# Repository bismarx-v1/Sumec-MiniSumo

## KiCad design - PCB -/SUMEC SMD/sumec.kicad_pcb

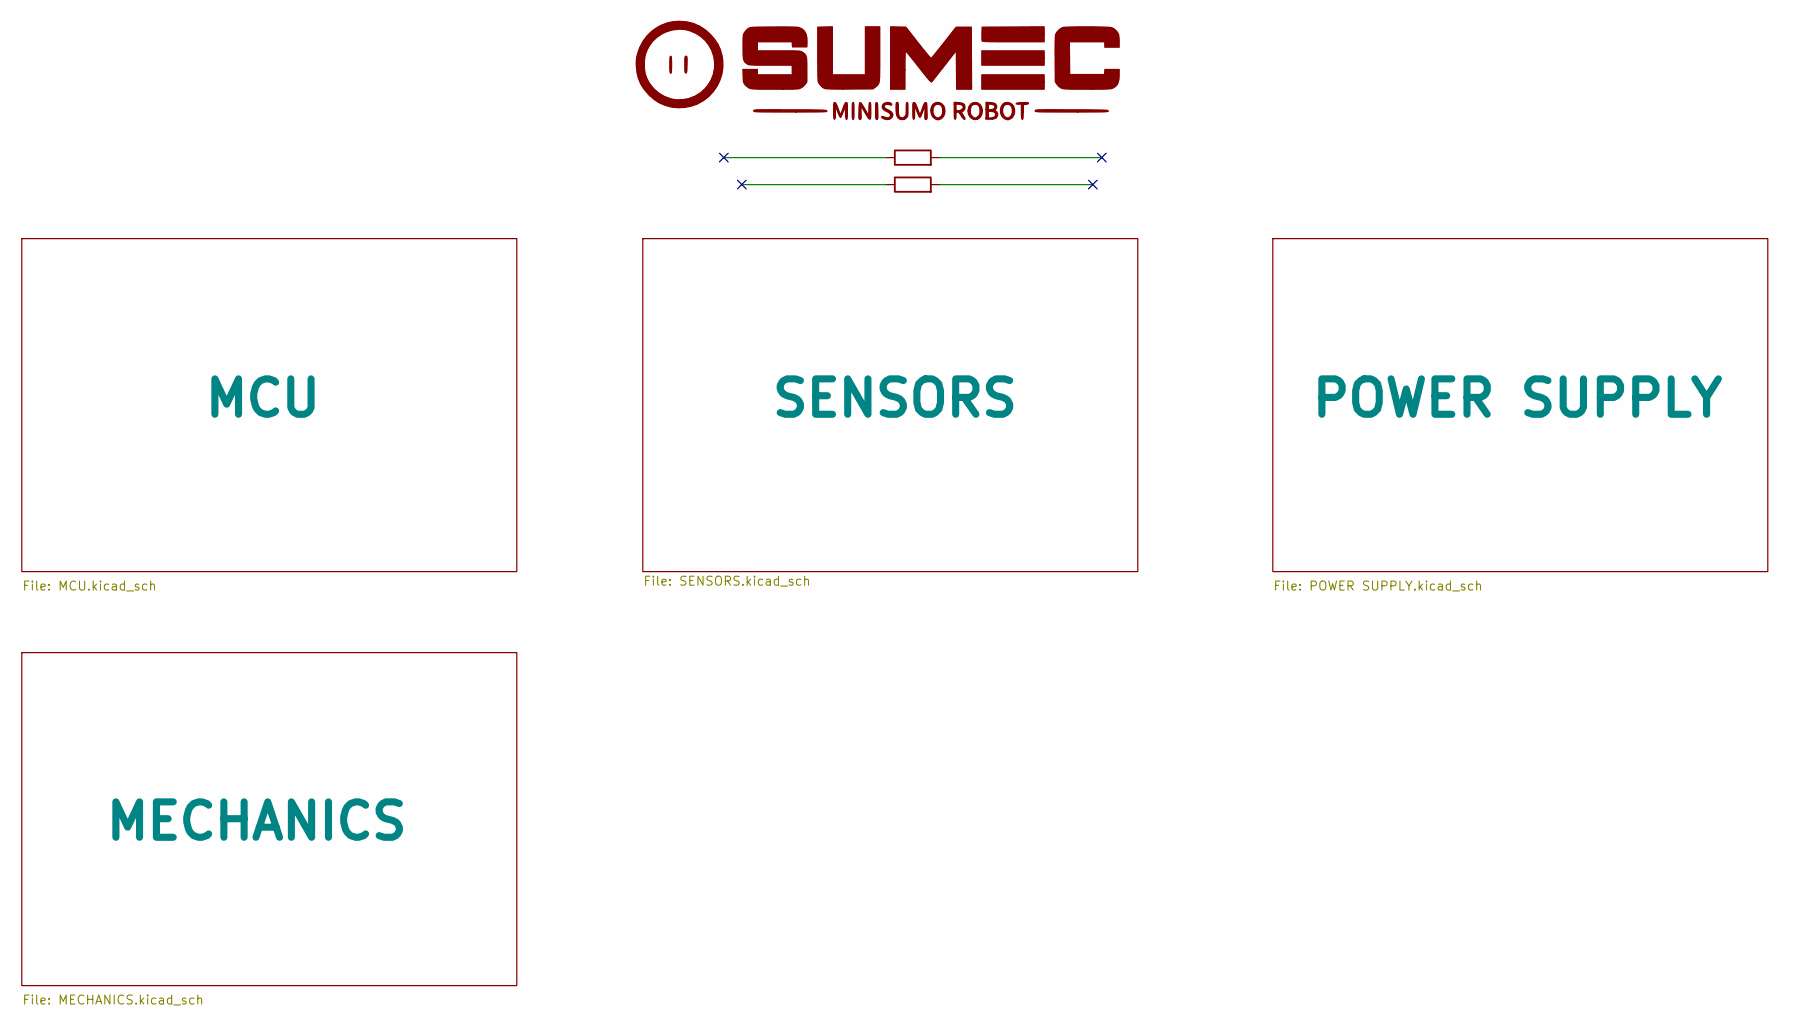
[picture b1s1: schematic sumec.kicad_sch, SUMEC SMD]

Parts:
R1: R; logo even smaller
R7: R; car cool smol

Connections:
+3V3: R7.2; also elsewhere on the board
EN: R7.1; also elsewhere on the board

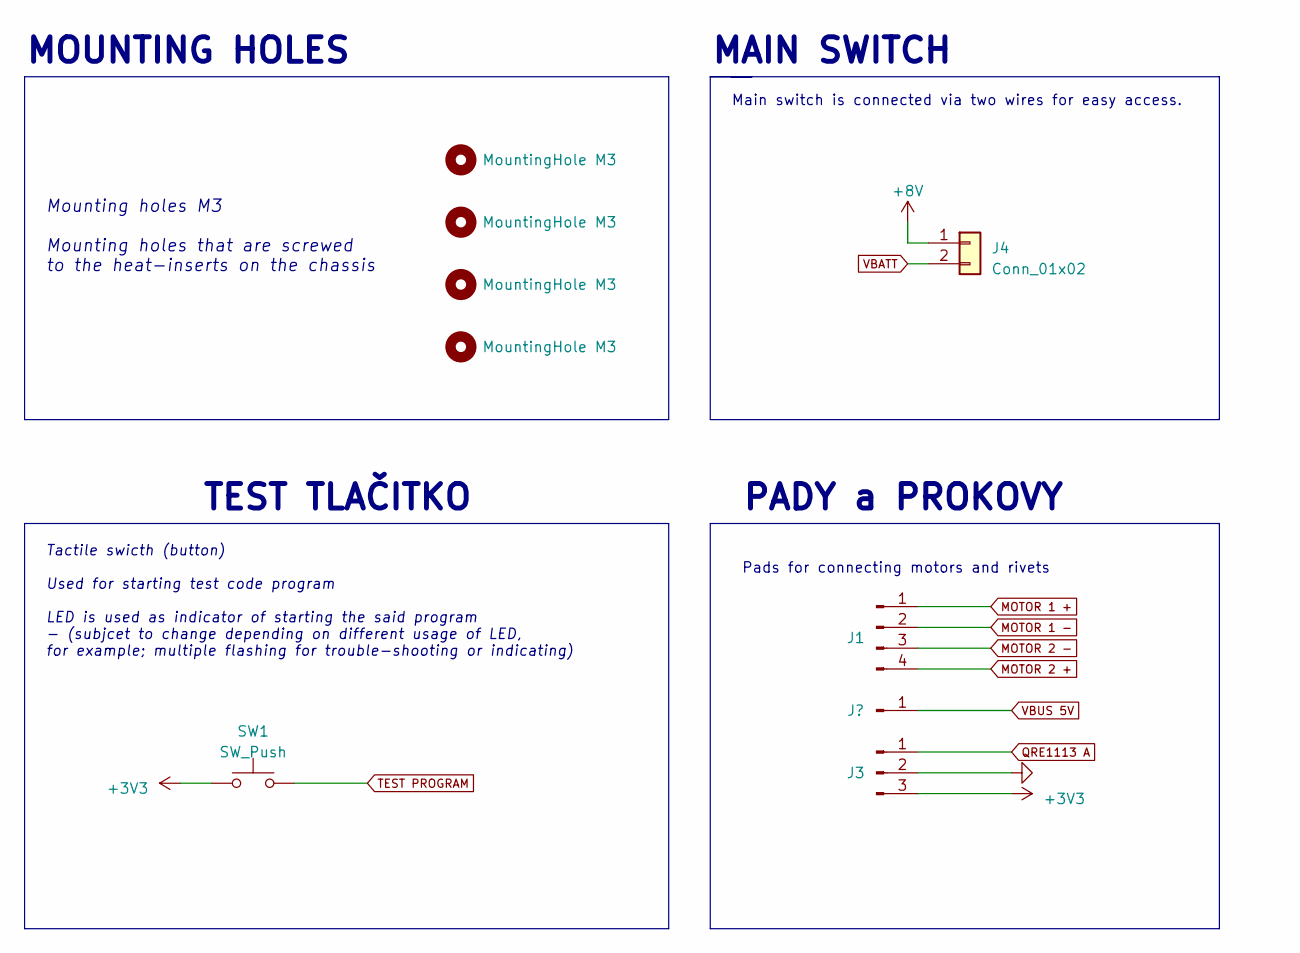
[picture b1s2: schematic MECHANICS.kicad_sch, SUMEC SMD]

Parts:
H1, H2, H3, H4: MountingHole M3; MountingHole_3.2mm_M3_ISO7380_Pad
J1: Conn_01x04_Pin; PinHeader_1x04_P2.54mm_Vertical
J2: Conn_01x01_Pin; SolderWire-0.1sqmm_1x01_D0.4mm_OD1mm
J3: Conn_01x03_Pin; PinSocket_1x03_P2.54mm_Vertical
J4: Conn_01x02; PinHeader_1x02_P2.54mm_Vertical
SW1: SW_Push; SW_SPST_B3U-1000P

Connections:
+3V3: J3.3, SW1.1; also elsewhere on the board
+8V: J4.1; also elsewhere on the board
GND: J3.2; also elsewhere on the board
MOTOR 1 +: J1.1; also elsewhere on the board
MOTOR 1 -: J1.2; also elsewhere on the board
MOTOR 2 +: J1.4; also elsewhere on the board
MOTOR 2 -: J1.3; also elsewhere on the board
QRE1113 A: J3.1; also elsewhere on the board
TEST PROGRAM: SW1.2; also elsewhere on the board
VBATT: J4.2; also elsewhere on the board
VBUS 5V: J2.1; also elsewhere on the board

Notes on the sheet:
MOUNTING HOLES
Pads for connecting motors and rivets
Mounting holes M3 Mounting holes that are screwed to the heat-inserts on the chassis
MAIN SWITCH
TEST TLAČITKO
Main switch is connected via two wires for easy access.
PADY a PROKOVY
Tactile swicth (button) Used for starting test code program LED is used as indicator of starting the said program - (subjcet to change depending on different usage of LED, for example; multiple flashing for trouble-shooting or indicating)

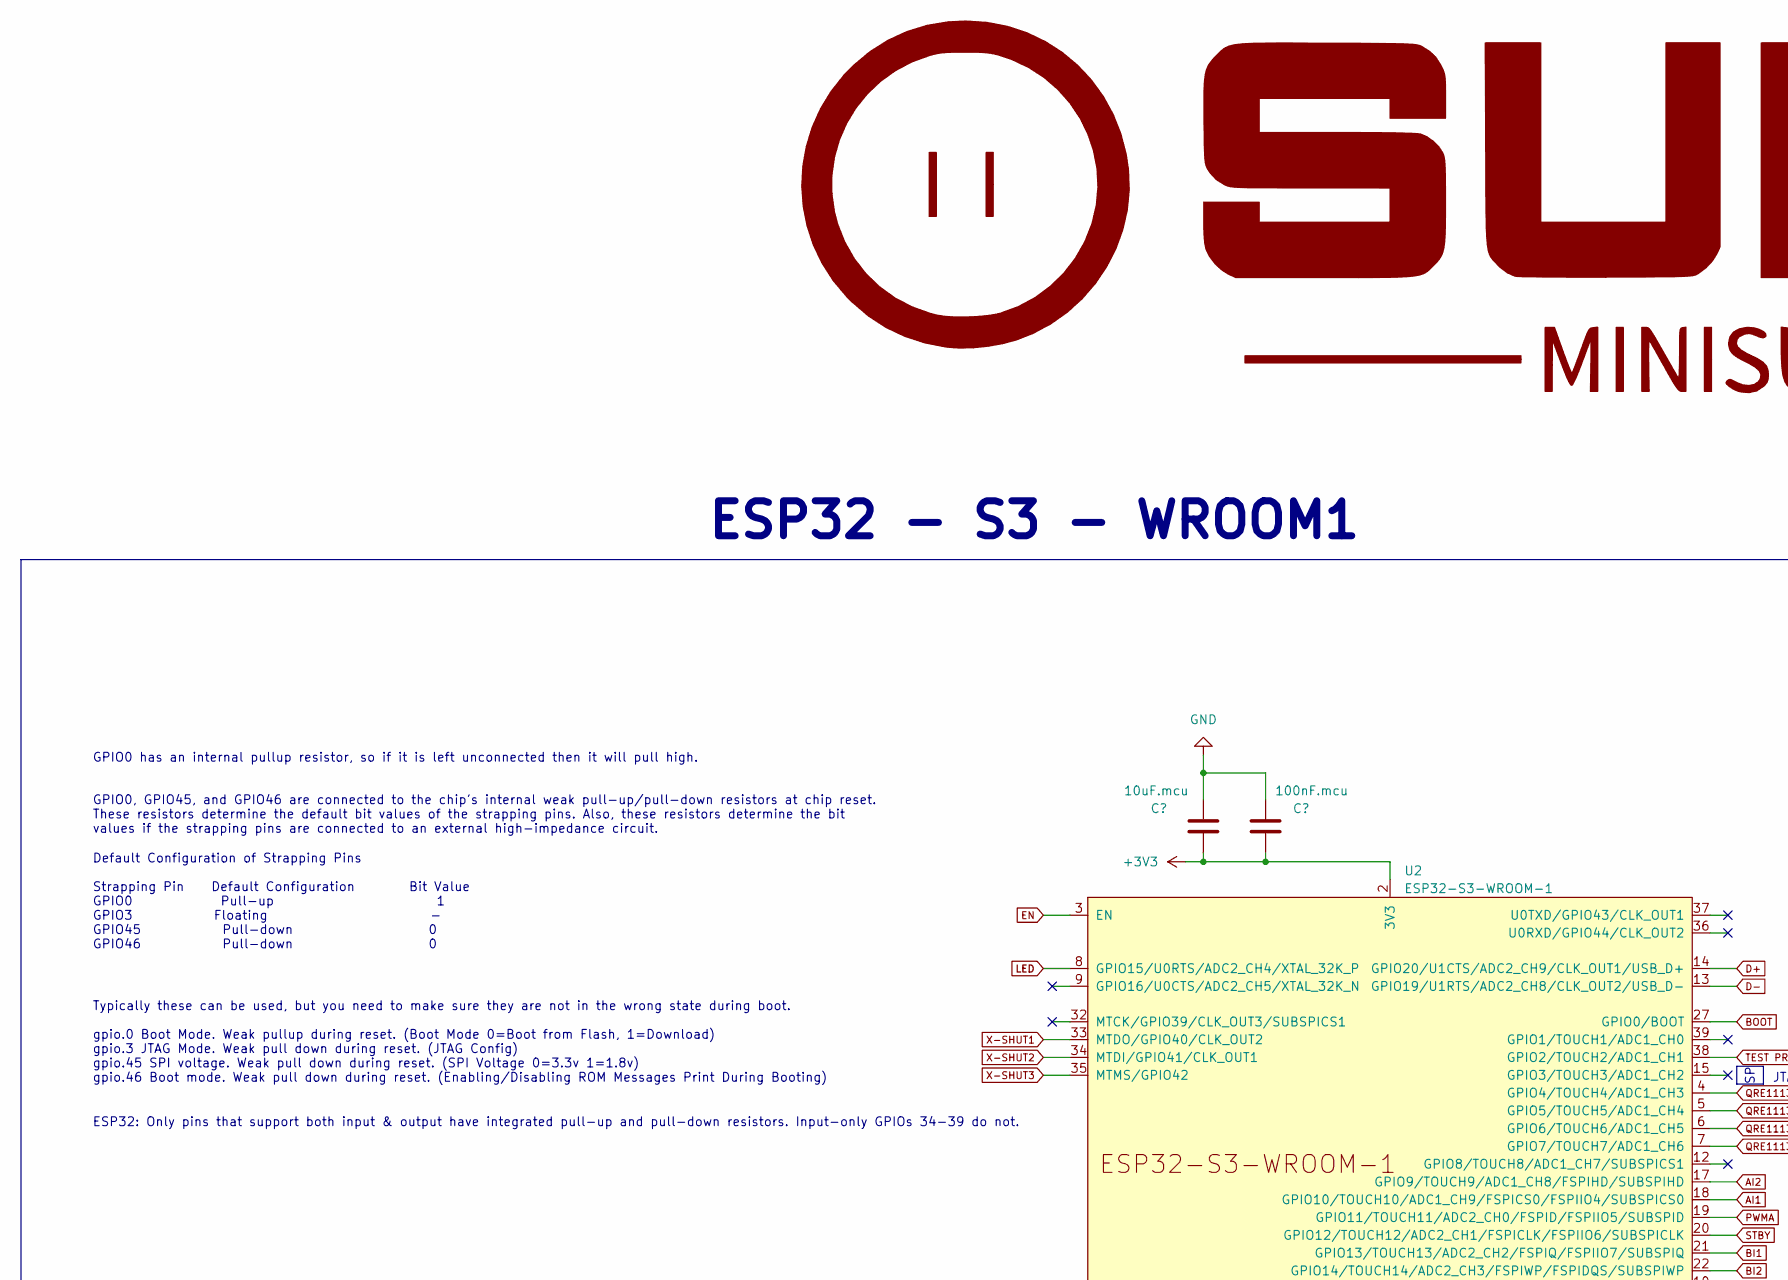
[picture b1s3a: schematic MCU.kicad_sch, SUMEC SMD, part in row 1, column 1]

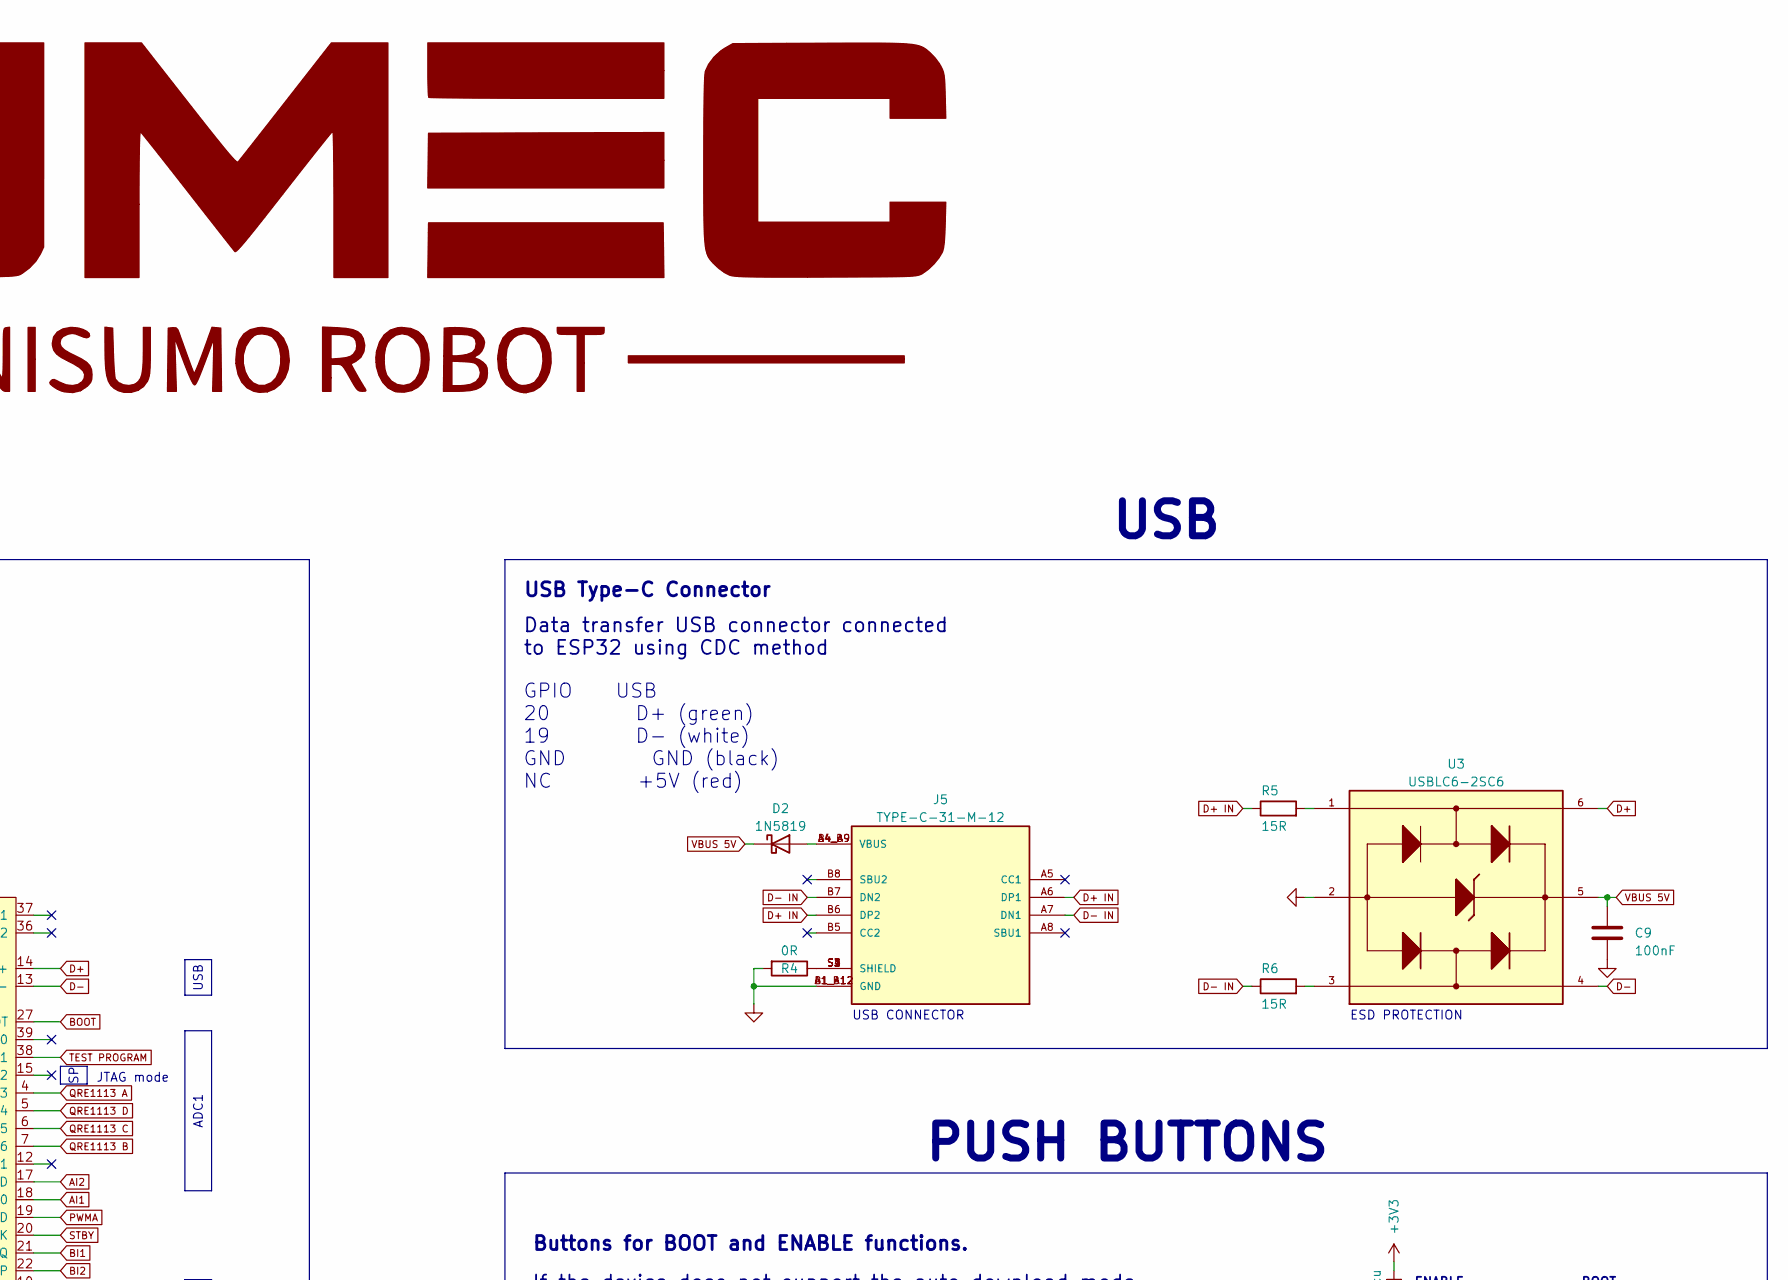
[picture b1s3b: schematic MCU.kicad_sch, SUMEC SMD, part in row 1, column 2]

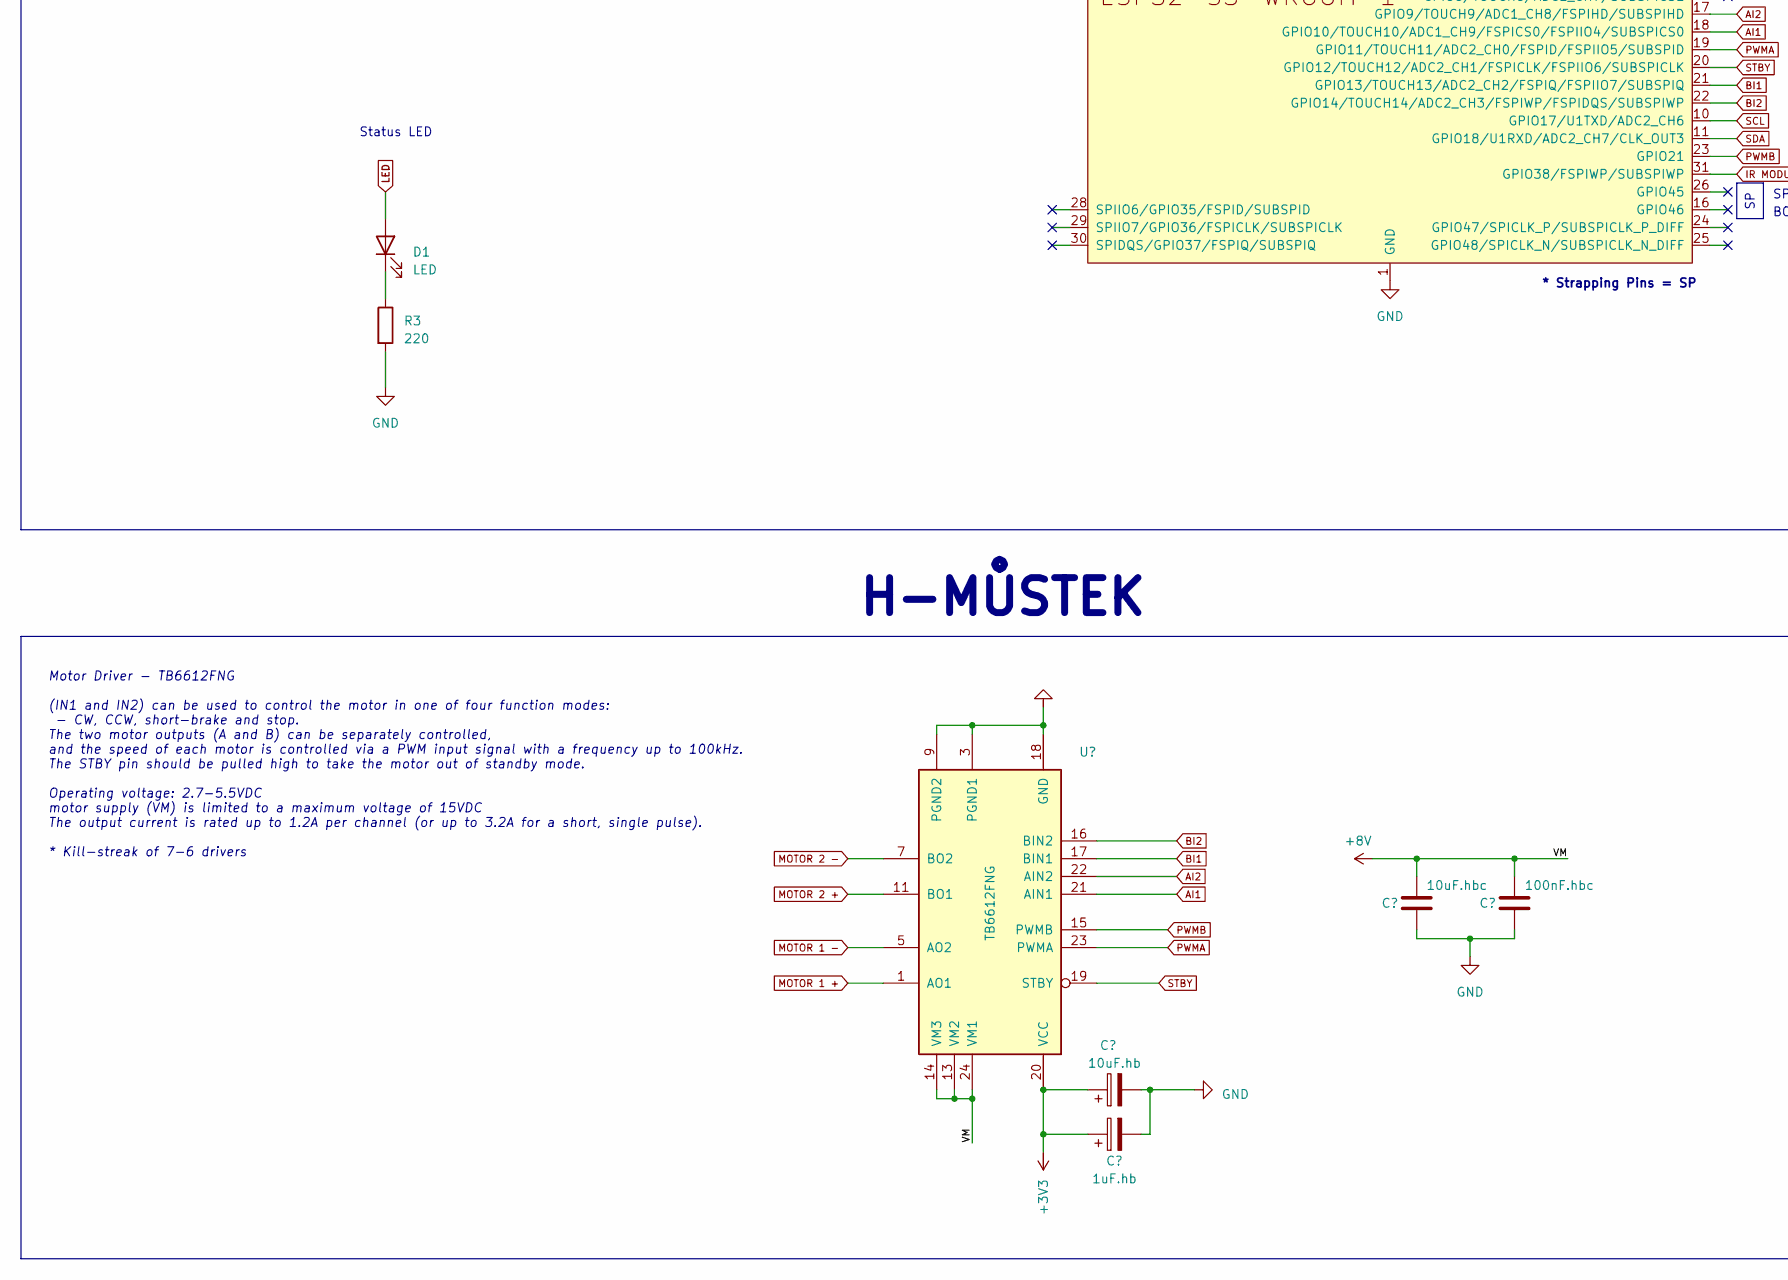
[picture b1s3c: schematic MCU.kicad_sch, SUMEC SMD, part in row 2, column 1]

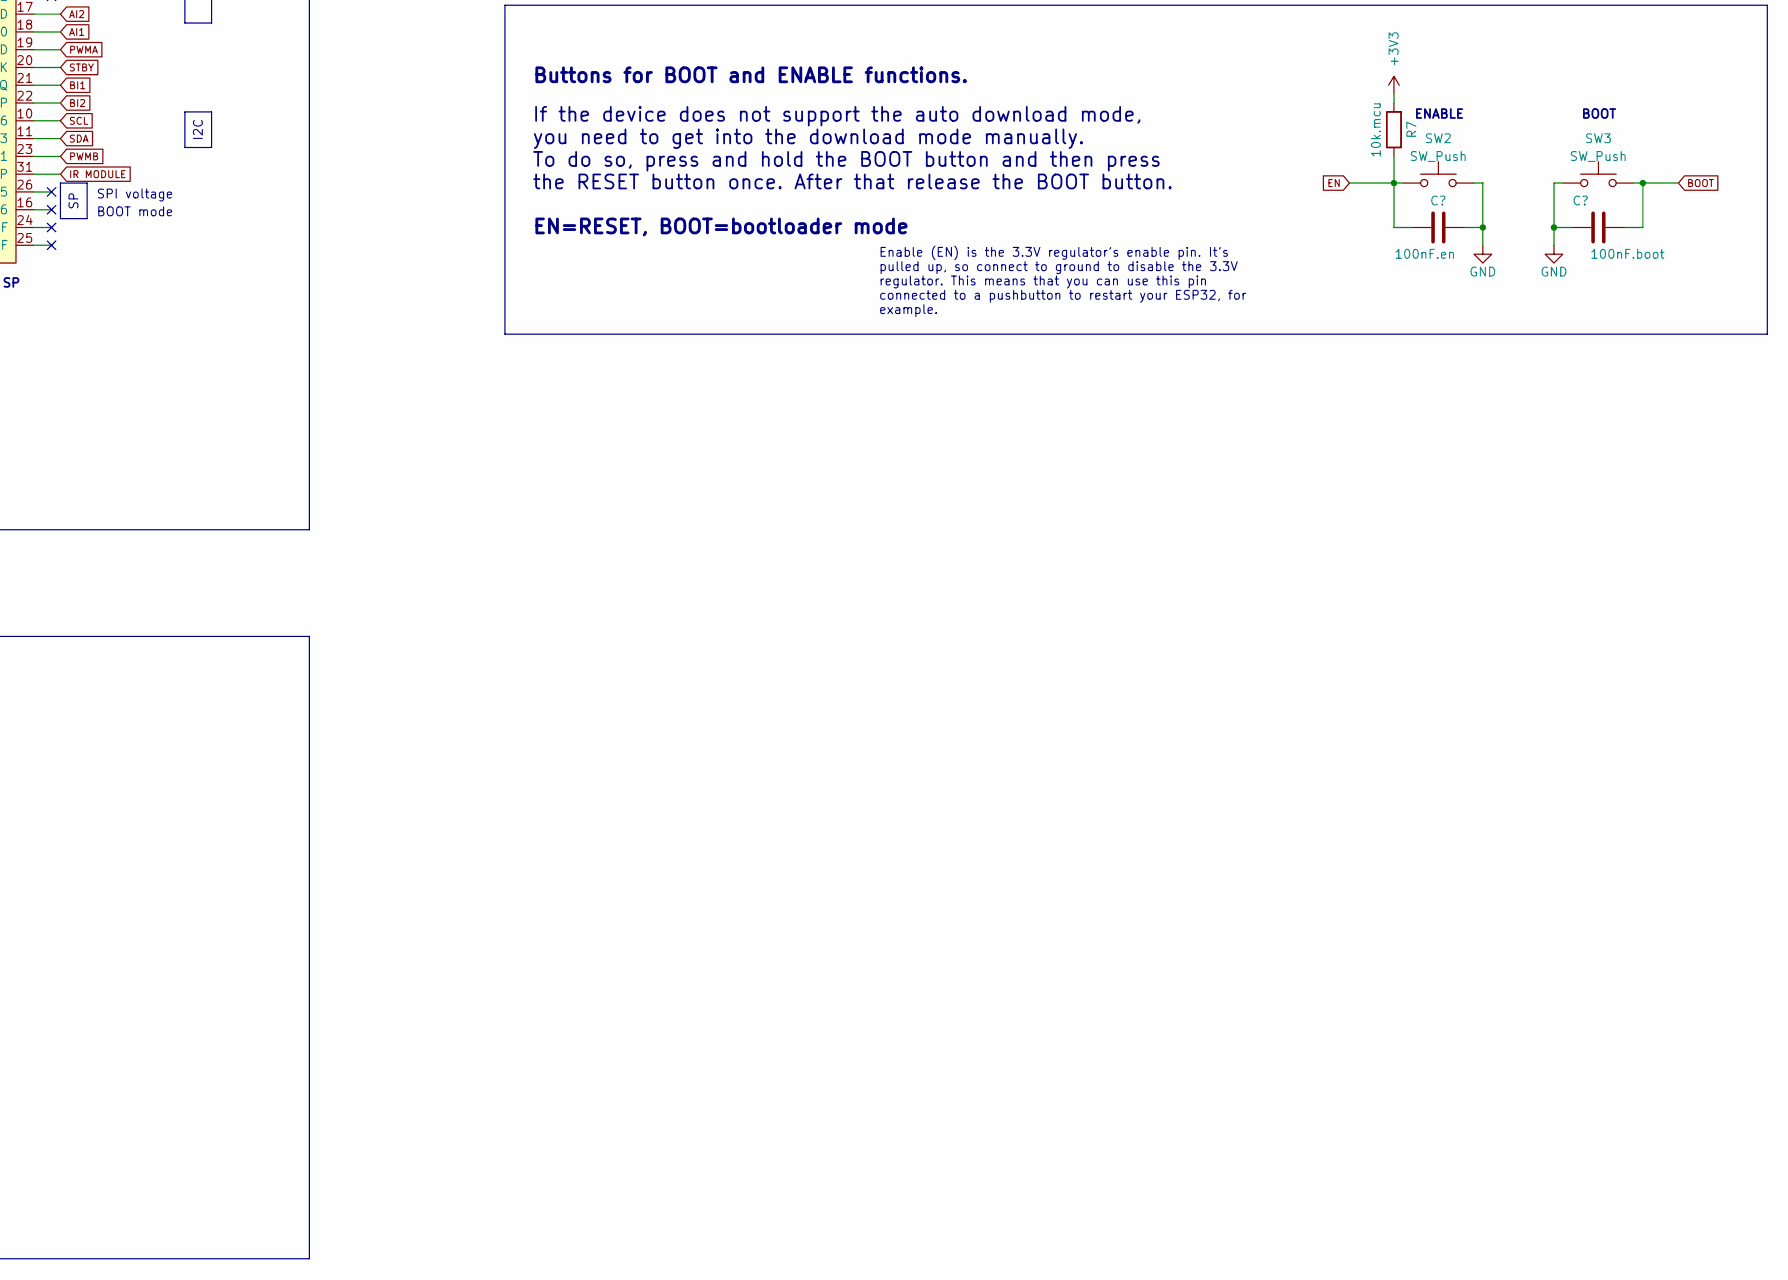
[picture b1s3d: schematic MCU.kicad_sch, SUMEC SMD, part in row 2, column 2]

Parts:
C1: 10uF.hb; C_1206_3216Metric
C2: 1uF.hb; C_1206_3216Metric
C3: 10uF.mcu; C_1206_3216Metric
C4: 100nF.mcu; C_1206_3216Metric
C5: 10uF.hbc; C_1206_3216Metric
C6: 100nF.hbc; C_1206_3216Metric
C7: 100nF.en; C_1206_3216Metric
C8: 100nF.boot; C_1206_3216Metric
C9: 100nF; C_1206_3216Metric
D1: LED; LED_1206_3216Metric_Pad1.42x1.75mm_HandSolder
D2: 1N5819; D_1206_3216Metric
J5: TYPE-C-31-M-12; HRO_TYPE-C-31-M-12; PARTREV 2020.12.08
R3: 220; R_1206_3216Metric_Pad1.30x1.75mm_HandSolder
R4: 0R; R_1206_3216Metric
R5, R6: 15R; R_1206_3216Metric
R7: 10k.mcu; R_1206_3216Metric
SW2, SW3: SW_Push; SW_SPST_B3U-1000P
U1: TB6612FNG; SSOP-24_5.3x8.2mm_P0.65mm
U2: ESP32-S3-WROOM-1
U3: USBLC6-2SC6; TSOT-23-6_HandSoldering

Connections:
+3V3: C1.1, C2.1, C3.1, C4.1, R7.2, U1.20 (VCC), U2.2 (3V3); also elsewhere on the board
+8V: C5.1, C6.1, U1.13 (VM2), U1.14 (VM3), U1.24 (VM1); also elsewhere on the board
AI1: U1.21 (AIN1), U2.18 (GPIO10/TOUCH10/ADC1_CH9/FSPICS0/FSPIIO4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)
AI2: U1.22 (AIN2), U2.17 (GPIO9/TOUCH9/ADC1_CH8/FSPIHD/SUBSPIHD)
BI1: U1.17 (BIN1), U2.21 (GPIO13/TOUCH13/ADC2_CH2/FSPIQ/FSPIIO7/S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)
BI2: U1.16 (BIN2), U2.22 (GPIO14/TOUCH14/ADC2_CH3/FSPIWP/FSPIDQS/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)
BOOT: C8.1, SW3.2, U2.27 (GPIO0/BOOT)
D+: U2.14 (GPIO20/U1CTS/ADC2_CH9/CLK_OUT1/USB_D+), U3.6
D+ IN: J5.A6 (DP1), J5.B6 (DP2), R5.1
D-: U2.13 (GPIO19/U1RTS/ADC2_CH8/CLK_OUT2/USB_D-), U3.4
D- IN: J5.A7 (DN1), J5.B7 (DN2), R6.1
EN: C7.1, R7.1, SW2.2, U2.3 (EN)
GND: C1.2, C2.2, C3.2, C4.2, C5.2, C6.2, C7.2, C8.2, C9.2, J5.A1_B12 (GND), J5.B1_A12 (GND), R3.2, R4.2, SW2.1, SW3.1, U1.3 (PGND1), U1.4 (PGND1), U1.9 (PGND2), U1.10 (PGND2), U1.18 (GND), U2.1 (GND), U2.40 (GND), U2.41 (GND), U3.2; also elsewhere on the board
IR MODULE: U2.31 (GPIO38/FSPIWP/SUBSPIWP); also elsewhere on the board
LED: D1.2 (A), U2.8 (GPIO15/U0RTS/ADC2_CH4/XTAL_32K_P)
MOTOR 1 +: U1.1 (AO1), U1.2 (AO1); also elsewhere on the board
MOTOR 1 -: U1.5 (AO2), U1.6 (AO2); also elsewhere on the board
MOTOR 2 +: U1.11 (BO1), U1.12 (BO1); also elsewhere on the board
MOTOR 2 -: U1.7 (BO2), U1.8 (BO2); also elsewhere on the board
unnamed: D1.1 (K), R3.1
unnamed: D2.2 (A), J5.A4_B9 (VBUS), J5.B4_A9 (VBUS)
unnamed: J5.S1 (SHIELD), J5.S2 (SHIELD), J5.S3 (SHIELD), J5.S4 (SHIELD), R4.1
unnamed: R5.2, U3.1
unnamed: R6.2, U3.3
PWMA: U1.23 (PWMA), U2.19 (GPIO11/TOUCH11/ADC2_CH0/FSPID/FSPIIO5/S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)
PWMB: U1.15 (PWMB), U2.23 (GPIO21)
QRE1113 A: U2.4 (GPIO4/TOUCH4/ADC1_CH3); also elsewhere on the board
QRE1113 B: U2.7 (GPIO7/TOUCH7/ADC1_CH6); also elsewhere on the board
QRE1113 C: U2.6 (GPIO6/TOUCH6/ADC1_CH5); also elsewhere on the board
QRE1113 D: U2.5 (GPIO5/TOUCH5/ADC1_CH4); also elsewhere on the board
SCL: U2.10 (GPIO17/U1TXD/ADC2_CH6); also elsewhere on the board
SDA: U2.11 (GPIO18/U1RXD/ADC2_CH7/CLK_OUT3); also elsewhere on the board
STBY: U1.19 (STBY), U2.20 (GPIO12/TOUCH12/ADC2_CH1/FSPICLK/FSPIIO6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)
TEST PROGRAM: U2.38 (GPIO2/TOUCH2/ADC1_CH1); also elsewhere on the board
VBUS 5V: C9.1, D2.1 (K), U3.5; also elsewhere on the board
X-SHUT1: U2.33 (MTDO/GPIO40/CLK_OUT2); also elsewhere on the board
X-SHUT2: U2.34 (MTDI/GPIO41/CLK_OUT1); also elsewhere on the board
X-SHUT3: U2.35 (MTMS/GPIO42); also elsewhere on the board

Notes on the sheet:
ADC1
USB
I2C
SPI voltage
Enable (EN) is the 3.3V regulator’s enable pin. It’s pulled up, so connect to ground to disable the 3.3V regulator. This means that you can use this pin connected to a pushbutton to restart your ESP32, for example.
USB CONNECTOR
USB Type-C Connector
GPIO0, GPIO45, and GPIO46 are connected to the chip's internal weak pull-up/pull-down resistors at chip reset. These resistors determine the default bit values of the strapping pins. Also, these resistors determine the bit values if the strapping pins are connected to an external high-impedance cir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
ENABLE
GPIO USB 20 D+ (green) 19 D- (white) GND GND (black) NC +5V (red)
H-MŮSTEK
Status LED
BOOT mode
If the device does not support the auto download mode, you need to get into the download mode manually. To do so, press and hold the BOOT button and then press the RESET button once. After that release the BOOT button.
Motor Driver - TB6612FNG (IN1 and IN2) can be used to control the motor in one of four function modes: - CW, CCW, short-brake and stop. The two motor outputs (A and B) can be separately controlled, and the speed of each motor is controlled via a PWM input signal with a frequency up to 100kHz. The S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
* Strapping Pins = SP
ESP32 - S3 - WROOM1
Default Configuration of Strapping Pins Strapping Pin Default Configuration Bit Value GPIO0 Pull-up 1 GPIO3 Floating - GPIO45 Pull-down 0 GPIO46 Pull-down 0
JTAG mode
PUSH BUTTONS
GPIO0 has an internal pullup resistor, so if it is left unconnected then it will pull high.
ESD PROTECTION
Buttons for BOOT and ENABLE functions.
Typically these can be used, but you need to make sure they are not in the wrong state during boot. gpio.0 Boot Mode. Weak pullup during reset. (Boot Mode 0=Boot from Flash, 1=Download) gpio.3 JTAG Mode. Weak pull down during reset. (JTAG Config) gpio.45 SPI voltage. Weak pull down during reset. (S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
ESP32: Only pins that support both input & output have integrated pull-up and pull-down resistors. Input-only GPIOs 34-39 do not.
EN=RESET, BOOT=bootloader mode
Data transfer USB connector connected to ESP32 using CDC method
BOOT

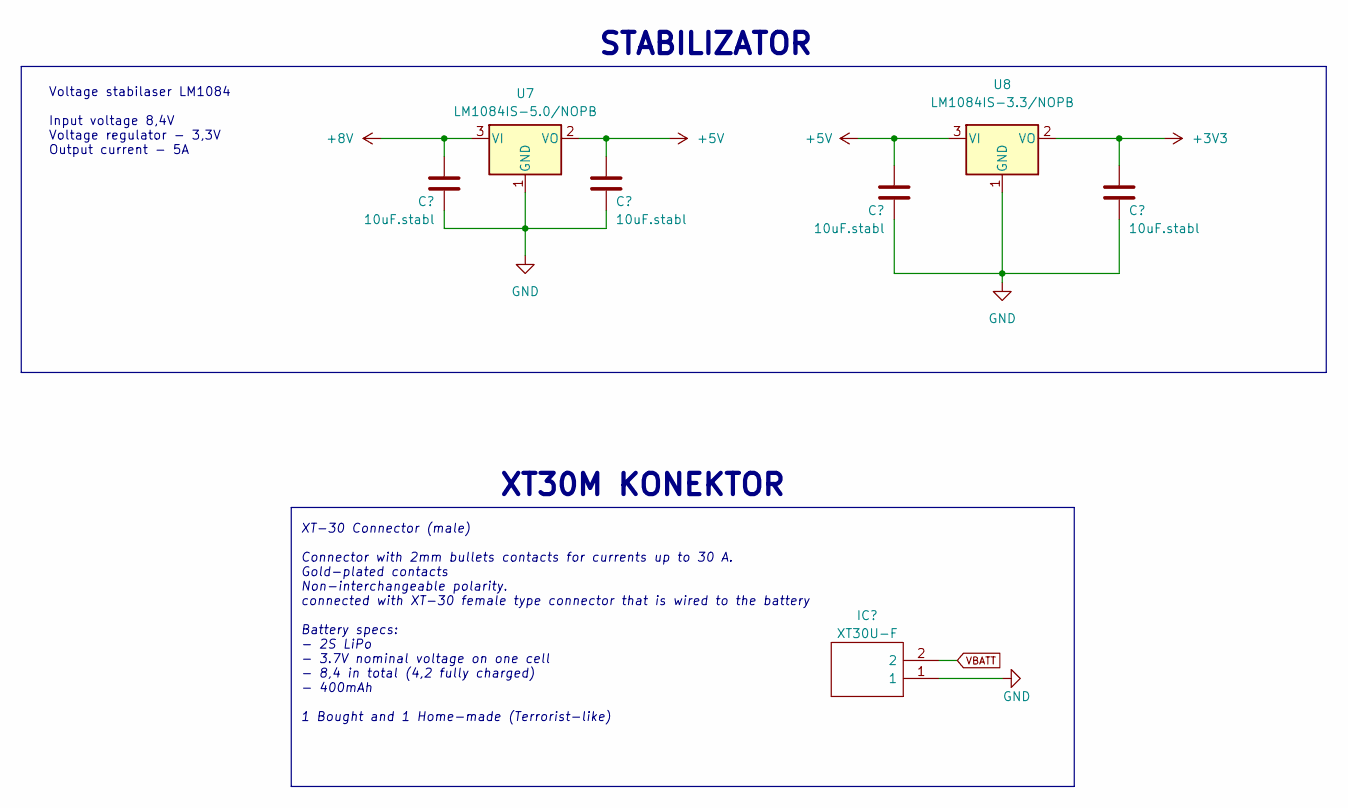
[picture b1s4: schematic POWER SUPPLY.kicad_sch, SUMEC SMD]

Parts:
C10, C11, C12, C13: 10uF.stabl; C_1206_3216Metric_Pad1.33x1.80mm_HandSolder
IC1: XT30U-F; AMASS_XT30U-M_1x02_P5.0mm_Vertical; Manufacturer_Part_Number XT30U-M; LCSC C99101
U7: LM1084IS-5.0/NOPB; TO-252-3_TabPin2
U8: LM1084IS-3.3/NOPB; TO-252-3_TabPin2

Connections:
+3V3: C13.1, U8.2 (VO); also elsewhere on the board
+5V: C11.1, C12.1, U7.2 (VO), U8.3 (VI); also elsewhere on the board
+8V: C10.1, U7.3 (VI); also elsewhere on the board
GND: C10.2, C11.2, C12.2, C13.2, IC1.1, U7.1 (GND), U8.1 (GND); also elsewhere on the board
VBATT: IC1.2; also elsewhere on the board

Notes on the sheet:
Voltage stabilaser LM1084 Input voltage 8,4V Voltage regulator - 3,3V Output current - 5A
XT-30 Connector (male) Connector with 2mm bullets contacts for currents up to 30 A. Gold-plated contacts Non-interchangeable polarity. connected with XT-30 female type connector that is wired to the battery Battery specs: - 2S LiPo - 3.7V nominal voltage on one cell - 8,4 in total (4,2 fully charge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
STABILIZATOR
XT30M KONEKTOR

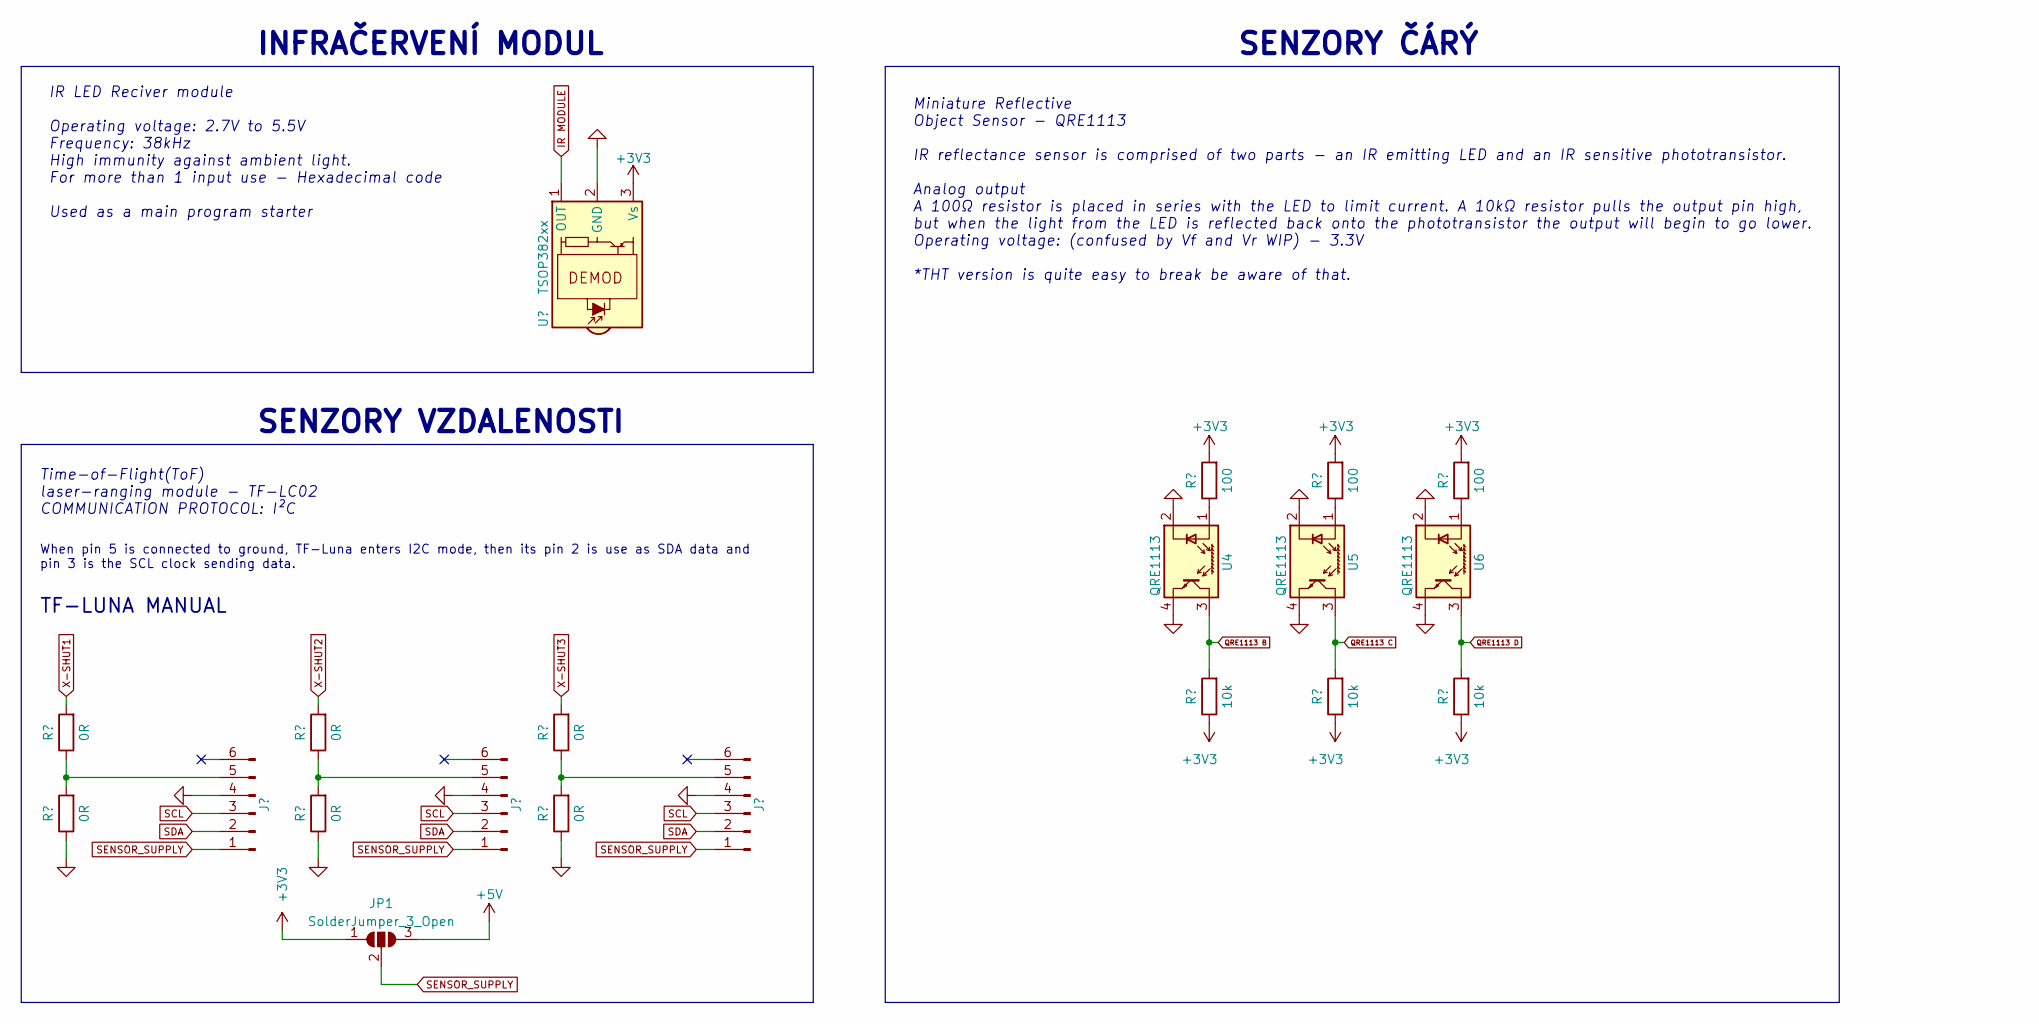
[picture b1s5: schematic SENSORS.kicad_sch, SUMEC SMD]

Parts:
J6, J7, J9: Conn_01x06_Pin; JST_SH_BM06B-SRSS-TB_1x06-1MP_P1.00mm_Vertical
J8: TSOP382xx; PinSocket_1x03_P2.54mm_Vertical
JP1: SolderJumper_3_Open; SolderJumper-3_P2.0mm_Open_TrianglePad1.0x1.5mm
R8, R9, R10, R11, R12, R13: 0R; R_1206_3216Metric
R14, R16, R18: 100; R_1206_3216Metric
R15, R17, R19: 10k; R_1206_3216Metric
U4, U5, U6: QRE1113; OnSemi_CASE100AQ - QRE1113

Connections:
+3V3: J8.3 (Vs), JP1.1 (A), R14.2, R15.1, R16.2, R17.1, R18.2, R19.1; also elsewhere on the board
+5V: JP1.3 (B); also elsewhere on the board
GND: J6.4, J7.4, J8.2 (GND), J9.4, R9.1, R11.1, R13.1, U4.2 (K), U4.4, U5.2 (K), U5.4, U6.2 (K), U6.4; also elsewhere on the board
IR MODULE: J8.1 (OUT); also elsewhere on the board
unnamed: J6.5, R8.1, R9.2
unnamed: J7.5, R10.1, R11.2
unnamed: J9.5, R12.1, R13.2
unnamed: R14.1, U4.1 (A)
unnamed: R16.1, U5.1 (A)
unnamed: R18.1, U6.1 (A)
QRE1113 B: R15.2, U4.3; also elsewhere on the board
QRE1113 C: R17.2, U5.3; also elsewhere on the board
QRE1113 D: R19.2, U6.3; also elsewhere on the board
SCL: J6.3, J7.3, J9.3; also elsewhere on the board
SDA: J6.2, J7.2, J9.2; also elsewhere on the board
SENSOR_SUPPLY: J6.1, J7.1, J9.1, JP1.2 (C)
X-SHUT1: R8.2; also elsewhere on the board
X-SHUT2: R10.2; also elsewhere on the board
X-SHUT3: R12.2; also elsewhere on the board

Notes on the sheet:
Time-of-Flight(ToF) laser-ranging module - TF-LC02 COMMUNICATION PROTOCOL: I²C
IR LED Reciver module Operating voltage: 2.7V to 5.5V Frequency: 38kHz High immunity against ambient light. For more than 1 input use - Hexadecimal code Used as a main program starter
INFRAČERVENÍ MODUL
SENZORY ČÁRÝ
When pin 5 is connected to ground, TF-Luna enters I2C mode, then its pin 2 is use as SDA data and pin 3 is the SCL clock sending data.
Miniature Reflective Object Sensor - QRE1113 IR reflectance sensor is comprised of two parts - an IR emitting LED and an IR sensitive phototransistor. Analog output A 100Ω resistor is placed in series with the LED to limit current. A 10kΩ resistor pulls the output pin high, but when the light from 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
TF-LUNA MANUAL
SENZORY VZDALENOSTI

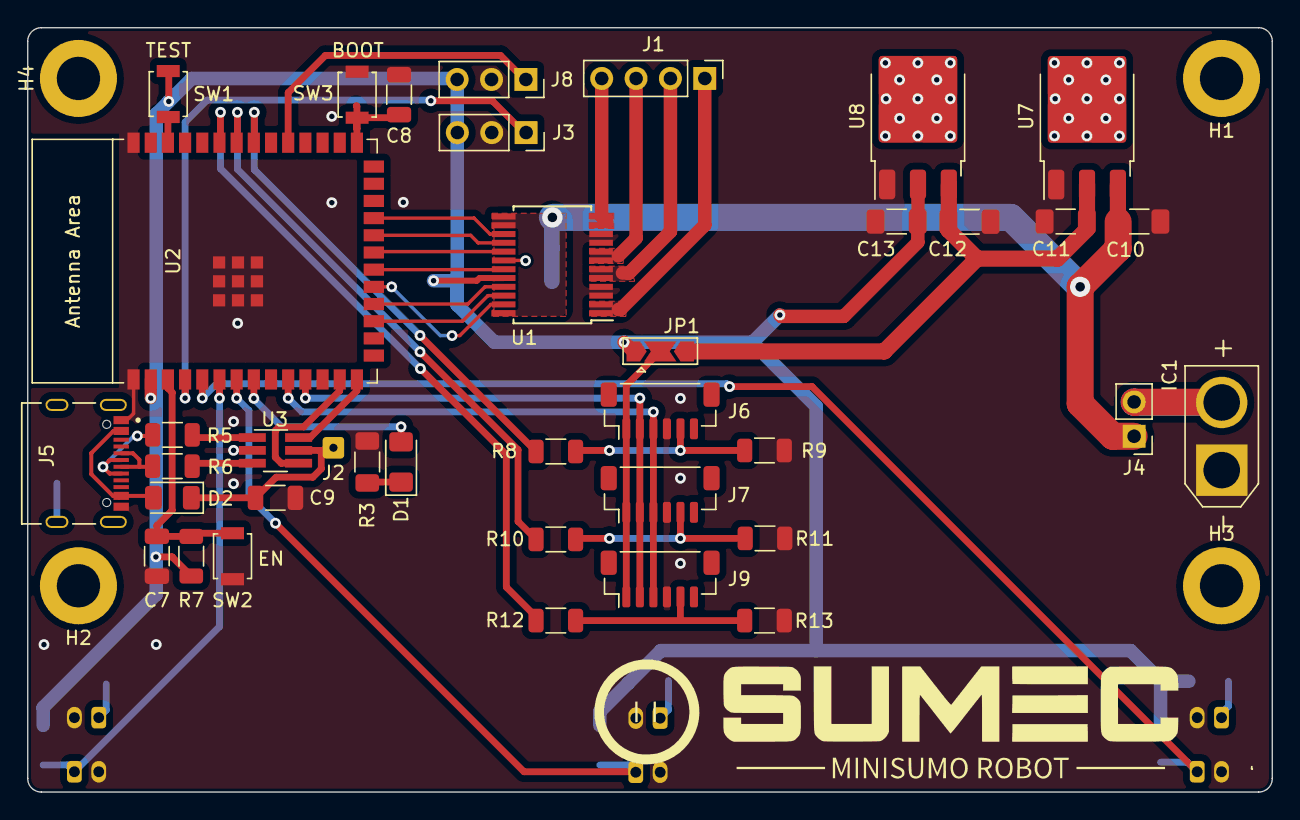
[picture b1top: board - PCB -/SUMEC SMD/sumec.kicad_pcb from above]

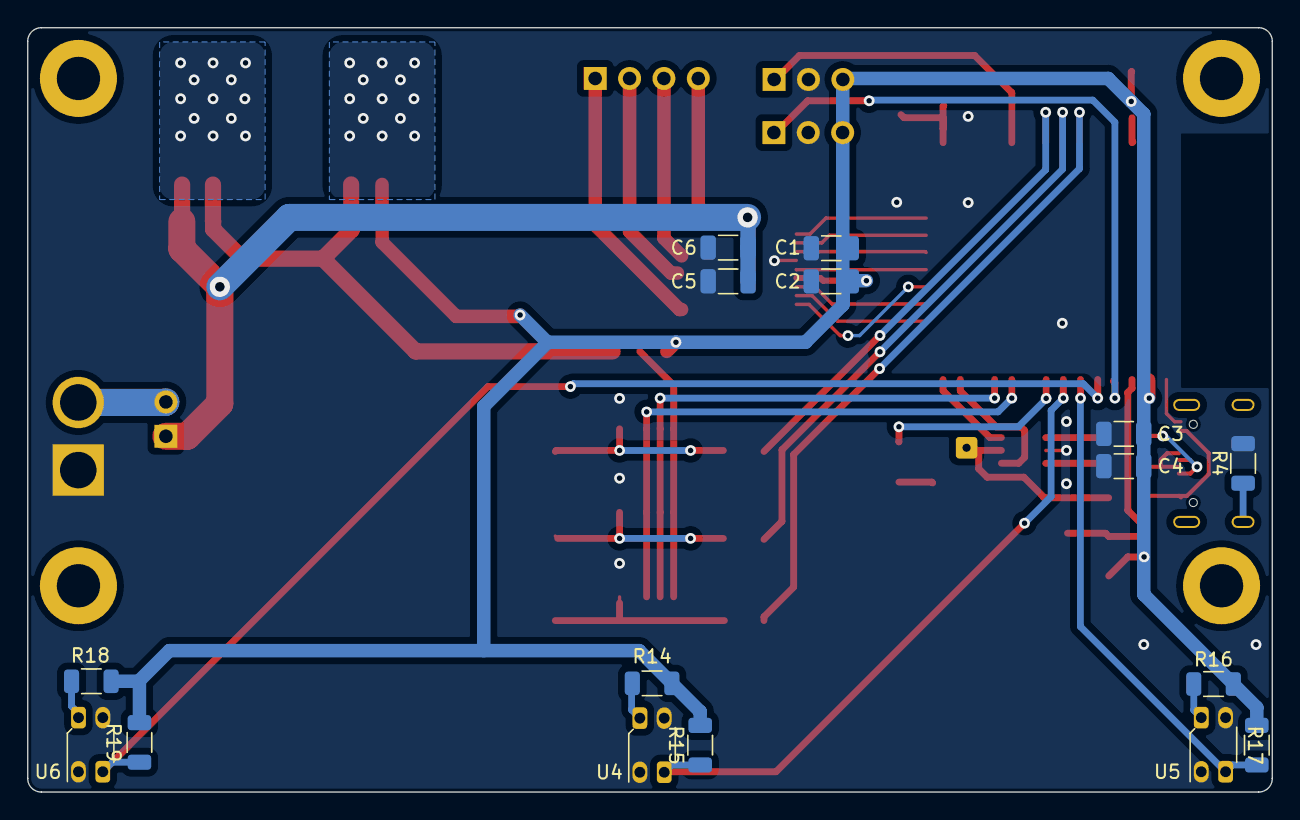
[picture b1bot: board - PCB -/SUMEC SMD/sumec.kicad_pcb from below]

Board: 2 copper layers, 92.0 x 56.5 mm, 59 parts (16 on the bottom side), 47 nets.
